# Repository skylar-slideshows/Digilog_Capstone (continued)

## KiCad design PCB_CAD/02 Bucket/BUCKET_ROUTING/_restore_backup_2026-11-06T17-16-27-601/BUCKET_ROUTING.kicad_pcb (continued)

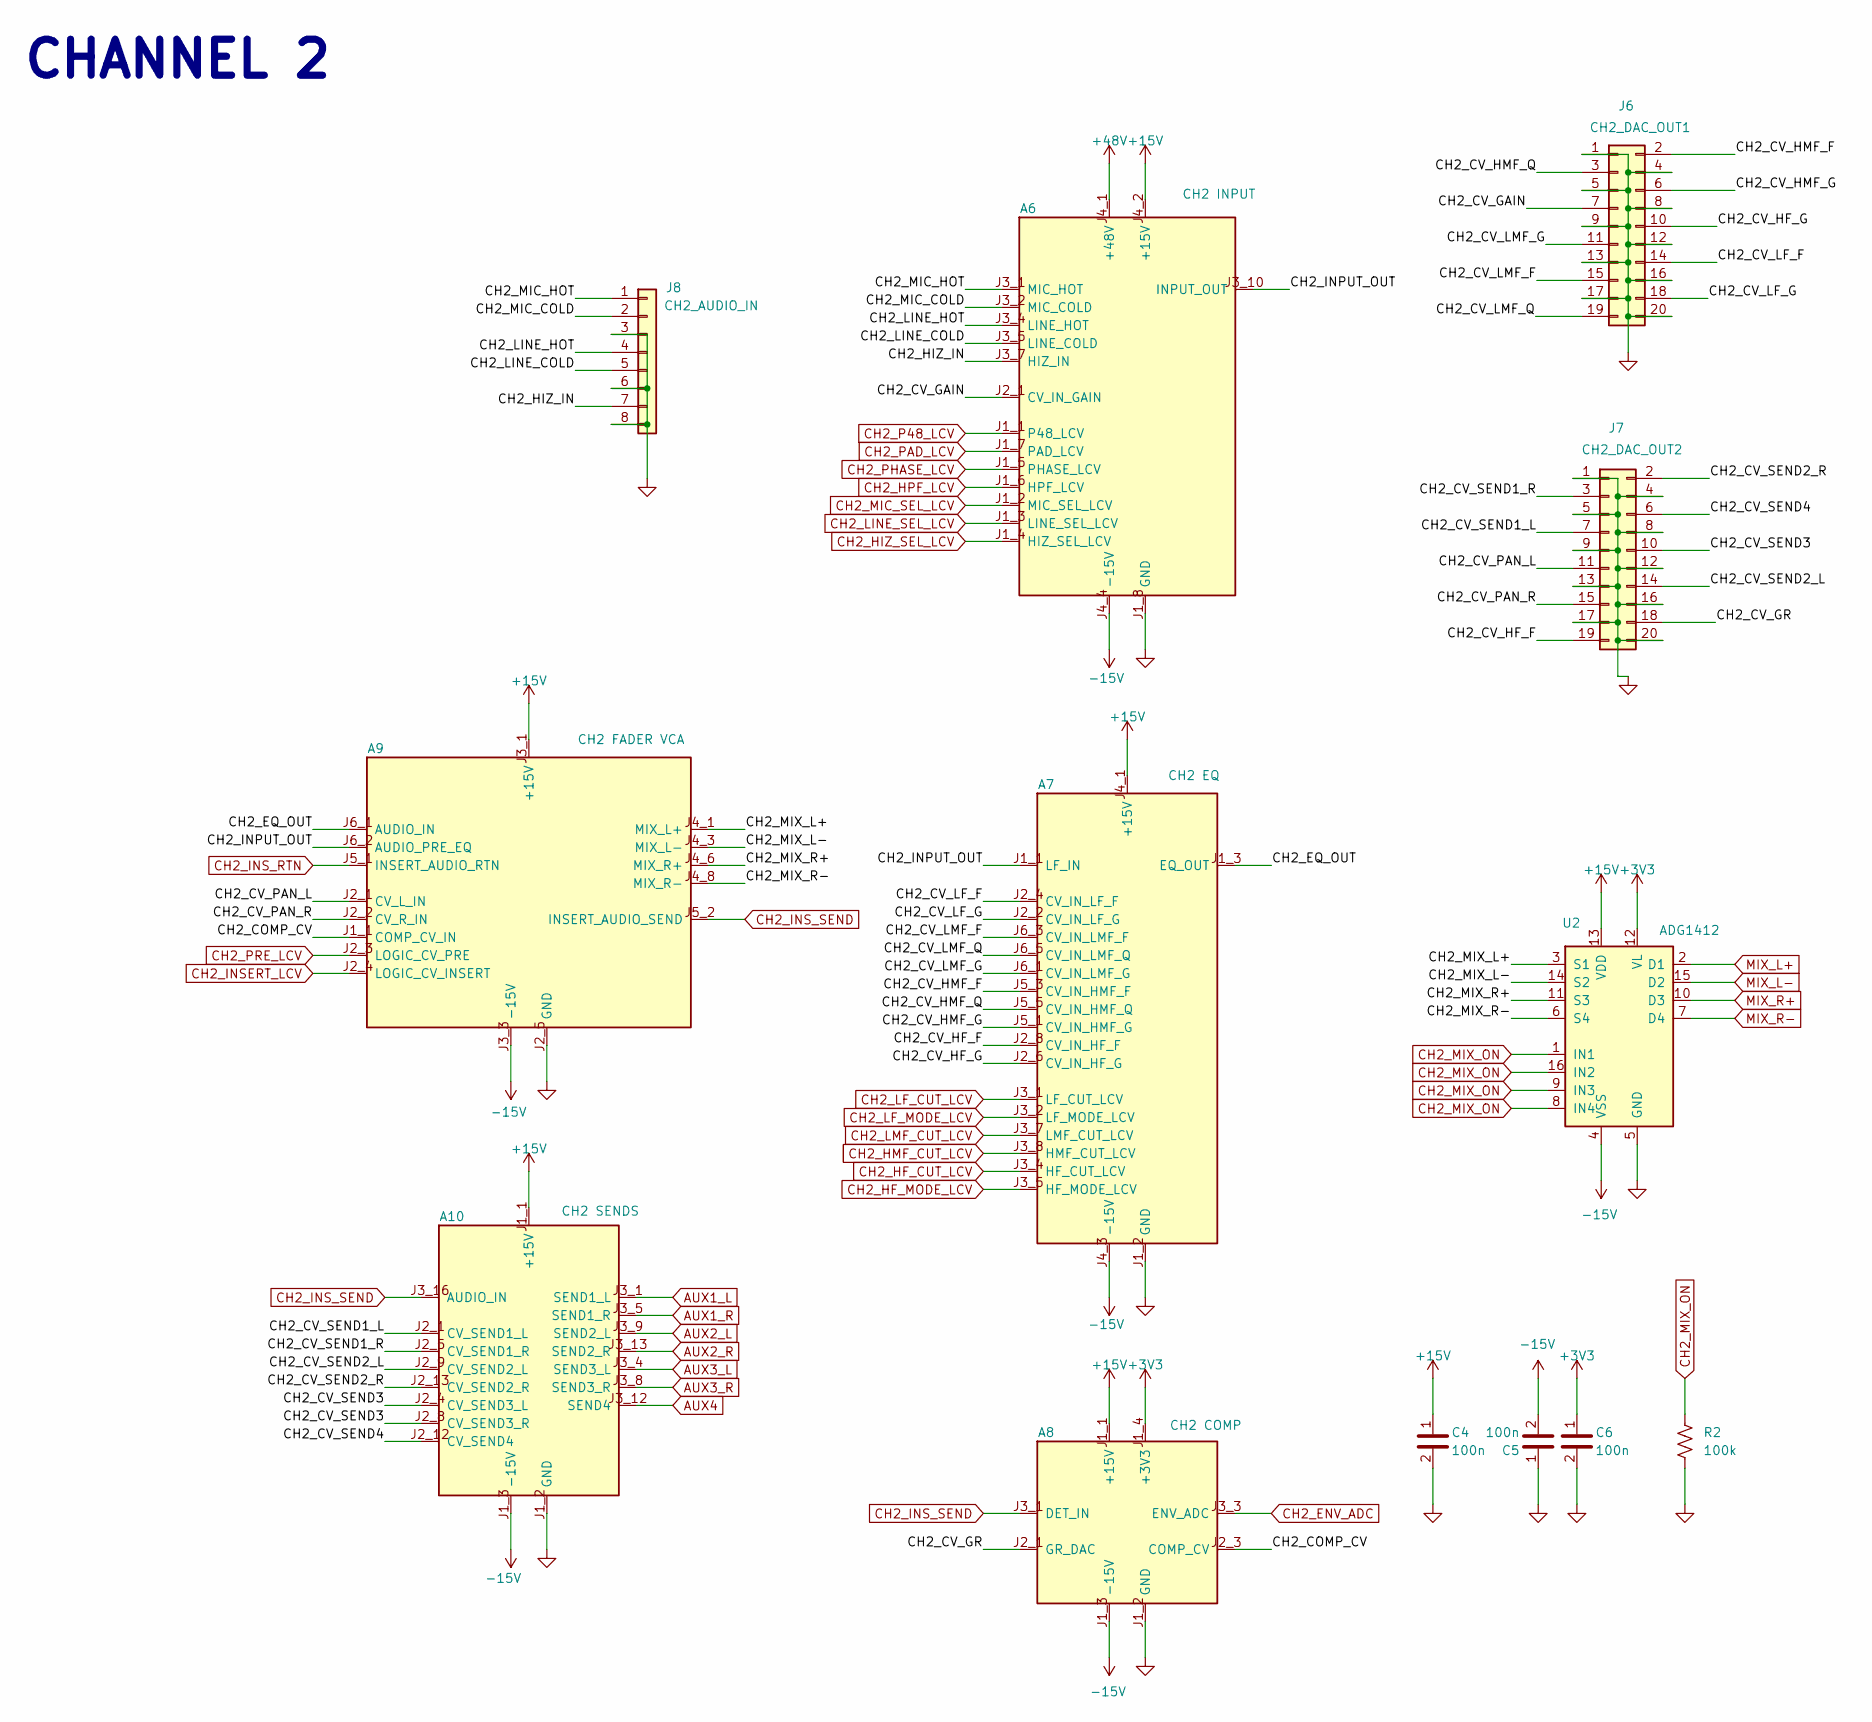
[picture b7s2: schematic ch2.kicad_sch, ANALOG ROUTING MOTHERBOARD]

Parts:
A6: CH2 INPUT; INPUT_CARD; LCSC dnp
A7: CH2 EQ; EQ_CARD; LCSC dnp
A8: CH2 COMP; COMP_CARD; LCSC dnp
A9: CH2 FADER VCA; FADER_VCA_CARD; LCSC dnp
A10: CH2 SENDS; SENDS_CARD; LCSC dnp
C4, C5, C6: 100n; C_0603_1608Metric; LCSC C1591
J6: CH2_DAC_OUT1; PinHeader_2x10_P1.27mm_Vertical; LCSC C42455943
J7: CH2_DAC_OUT2; PinHeader_2x10_P1.27mm_Vertical; LCSC C42455943
J8: CH2_AUDIO_IN; PinHeader_1x08_P2.54mm_Vertical; LCSC C54620384
R2: 100k; R_0603_1608Metric; LCSC C122538
U2: ADG1412; TSSOP-16_4.4x5mm_P0.65mm; LCSC C206604

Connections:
+3V3: A8.J1_4 (+3V3), C6.1, U2.12 (VL); also elsewhere on the board
+15V: A6.J4_2 (+15V), A7.J4_1 (+15V), A8.J1_1 (+15V), A9.J3_1 (+15V), A10.J1_1 (+15V), C4.1, U2.13 (VDD); also elsewhere on the board
+48V: A6.J4_1 (+48V); also elsewhere on the board
-15V: A6.J4_4 (-15V), A7.J4_3 (-15V), A8.J1_3 (-15V), A9.J3_3 (-15V), A10.J1_3 (-15V), C5.2, U2.4 (VSS); also elsewhere on the board
/CH2/CH2_COMP_CV: A8.J2_3 (COMP_CV), A9.J1_1 (COMP_CV_IN)
/CH2/CH2_CV_GAIN: A6.J2_1 (CV_IN_GAIN), J6.7
/CH2/CH2_CV_GR: A8.J2_1 (GR_DAC), J7.18
/CH2/CH2_CV_HF_F: A7.J2_8 (CV_IN_HF_F), J7.19
/CH2/CH2_CV_HF_G: A7.J2_6 (CV_IN_HF_G), J6.10
/CH2/CH2_CV_HMF_F: A7.J5_3 (CV_IN_HMF_F), J6.2
/CH2/CH2_CV_HMF_G: A7.J5_1 (CV_IN_HMF_G), J6.6
/CH2/CH2_CV_HMF_Q: A7.J5_5 (CV_IN_HMF_Q), J6.3
/CH2/CH2_CV_LF_F: A7.J2_4 (CV_IN_LF_F), J6.14
/CH2/CH2_CV_LF_G: A7.J2_2 (CV_IN_LF_G), J6.18
/CH2/CH2_CV_LMF_F: A7.J6_3 (CV_IN_LMF_F), J6.15
/CH2/CH2_CV_LMF_G: A7.J6_1 (CV_IN_LMF_G), J6.11
/CH2/CH2_CV_LMF_Q: A7.J6_5 (CV_IN_LMF_Q), J6.19
/CH2/CH2_CV_PAN_L: A9.J2_1 (CV_L_IN), J7.11
/CH2/CH2_CV_PAN_R: A9.J2_2 (CV_R_IN), J7.15
/CH2/CH2_CV_SEND1_L: A10.J2_1 (CV_SEND1_L), J7.7
/CH2/CH2_CV_SEND1_R: A10.J2_5 (CV_SEND1_R), J7.3
/CH2/CH2_CV_SEND2_L: A10.J2_9 (CV_SEND2_L), J7.14
/CH2/CH2_CV_SEND2_R: A10.J2_13 (CV_SEND2_R), J7.2
/CH2/CH2_CV_SEND3: A10.J2_4 (CV_SEND3_L), A10.J2_8 (CV_SEND3_R), J7.10
/CH2/CH2_CV_SEND4: A10.J2_12 (CV_SEND4), J7.6
/CH2/CH2_EQ_OUT: A7.J1_3 (EQ_OUT), A9.J6_1 (AUDIO_IN)
/CH2/CH2_HIZ_IN: A6.J3_7 (HIZ_IN), J8.7
/CH2/CH2_INPUT_OUT: A6.J3_10 (INPUT_OUT), A7.J1_1 (LF_IN), A9.J6_2 (AUDIO_PRE_EQ)
/CH2/CH2_LINE_COLD: A6.J3_5 (LINE_COLD), J8.5
/CH2/CH2_LINE_HOT: A6.J3_4 (LINE_HOT), J8.4
/CH2/CH2_MIC_COLD: A6.J3_2 (MIC_COLD), J8.2
/CH2/CH2_MIC_HOT: A6.J3_1 (MIC_HOT), J8.1
/CH2/CH2_MIX_L+: A9.J4_1 (MIX_L+), U2.3 (S1)
/CH2/CH2_MIX_L-: A9.J4_3 (MIX_L-), U2.14 (S2)
/CH2/CH2_MIX_R+: A9.J4_6 (MIX_R+), U2.11 (S3)
/CH2/CH2_MIX_R-: A9.J4_8 (MIX_R-), U2.6 (S4)
AUX1_L: A10.J3_1 (SEND1_L); also elsewhere on the board
AUX1_R: A10.J3_5 (SEND1_R); also elsewhere on the board
AUX2_L: A10.J3_9 (SEND2_L); also elsewhere on the board
AUX2_R: A10.J3_13 (SEND2_R); also elsewhere on the board
AUX3_L: A10.J3_4 (SEND3_L); also elsewhere on the board
AUX3_R: A10.J3_8 (SEND3_R); also elsewhere on the board
AUX4: A10.J3_12 (SEND4); also elsewhere on the board
CH2_ENV_ADC: A8.J3_3 (ENV_ADC); also elsewhere on the board
CH2_HF_CUT_LCV: A7.J3_4 (HF_CUT_LCV); also elsewhere on the board
CH2_HF_MODE_LCV: A7.J3_5 (HF_MODE_LCV); also elsewhere on the board
CH2_HIZ_SEL_LCV: A6.J1_4 (HIZ_SEL_LCV); also elsewhere on the board
CH2_HMF_CUT_LCV: A7.J3_8 (HMF_CUT_LCV); also elsewhere on the board
CH2_HPF_LCV: A6.J1_6 (HPF_LCV); also elsewhere on the board
CH2_INSERT_LCV: A9.J2_4 (LOGIC_CV_INSERT); also elsewhere on the board
CH2_INS_RTN: A9.J5_1 (INSERT_AUDIO_RTN); also elsewhere on the board
CH2_INS_SEND: A8.J3_1 (DET_IN), A9.J5_2 (INSERT_AUDIO_SEND), A10.J3_16 (AUDIO_IN); also elsewhere on the board
CH2_LF_CUT_LCV: A7.J3_1 (LF_CUT_LCV); also elsewhere on the board
CH2_LF_MODE_LCV: A7.J3_2 (LF_MODE_LCV); also elsewhere on the board
CH2_LINE_SEL_LCV: A6.J1_3 (LINE_SEL_LCV); also elsewhere on the board
CH2_LMF_CUT_LCV: A7.J3_7 (LMF_CUT_LCV); also elsewhere on the board
CH2_MIC_SEL_LCV: A6.J1_2 (MIC_SEL_LCV); also elsewhere on the board
CH2_MIX_ON: R2.1, U2.1 (IN1), U2.8 (IN4), U2.9 (IN3), U2.16 (IN2); also elsewhere on the board
CH2_P48_LCV: A6.J1_1 (P48_LCV); also elsewhere on the board
CH2_PAD_LCV: A6.J1_7 (PAD_LCV); also elsewhere on the board
CH2_PHASE_LCV: A6.J1_5 (PHASE_LCV); also elsewhere on the board
CH2_PRE_LCV: A9.J2_3 (LOGIC_CV_PRE); also elsewhere on the board
GND: A6.J1_8 (GND), A6.J2_2 (GND), A6.J3_3 (GND), A6.J3_6 (GND), A6.J3_8 (GND), A6.J3_9 (GND), A6.J4_3 (GND), A7.J1_2 (GND), A7.J1_4 (GND), A7.J2_1 (GND), A7.J2_3 (GND), A7.J2_5 (GND), A7.J2_7 (GND), A7.J3_3 (GND), A7.J3_6 (GND), A7.J4_2 (GND), A7.J5_2 (GND), A7.J5_4 (GND), A7.J5_6 (GND), A7.J6_2 (GND), A7.J6_4 (GND), A7.J6_6 (GND), A8.J1_2 (GND), A8.J2_2 (GND), A8.J2_4 (GND), A8.J3_2 (GND), A8.J3_4 (GND), A9.J1_2 (GND), A9.J2_5 (GND), A9.J3_2 (GND), A9.J4_2 (GND), A9.J4_4 (GND), A9.J4_5 (GND), A9.J4_7 (GND), A9.J5_3 (GND), A9.J6_3 (GND), A10.J1_2 (GND), A10.J2_2 (GND), A10.J2_3 (GND), A10.J2_6 (GND), A10.J2_7 (GND), A10.J2_10 (GND), A10.J2_11 (GND), A10.J2_14 (GND), A10.J3_2 (GND), A10.J3_3 (GND), A10.J3_6 (GND), A10.J3_7 (GND), A10.J3_10 (GND), A10.J3_11 (GND), A10.J3_14 (GND), A10.J3_15 (GND), C4.2, C5.1, C6.2, J6.1, J6.4, J6.5, J6.8, J6.9, J6.12, J6.13, J6.16, J6.17, J6.20, J7.1, J7.4, J7.5, J7.8, J7.9, J7.12, J7.13, J7.16, J7.17, J7.20, J8.3, J8.6, J8.8, R2.2, U2.5 (GND); also elsewhere on the board
MIX_L+: U2.2 (D1); also elsewhere on the board
MIX_L-: U2.15 (D2); also elsewhere on the board
MIX_R+: U2.10 (D3); also elsewhere on the board
MIX_R-: U2.7 (D4); also elsewhere on the board

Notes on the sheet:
CHANNEL 2

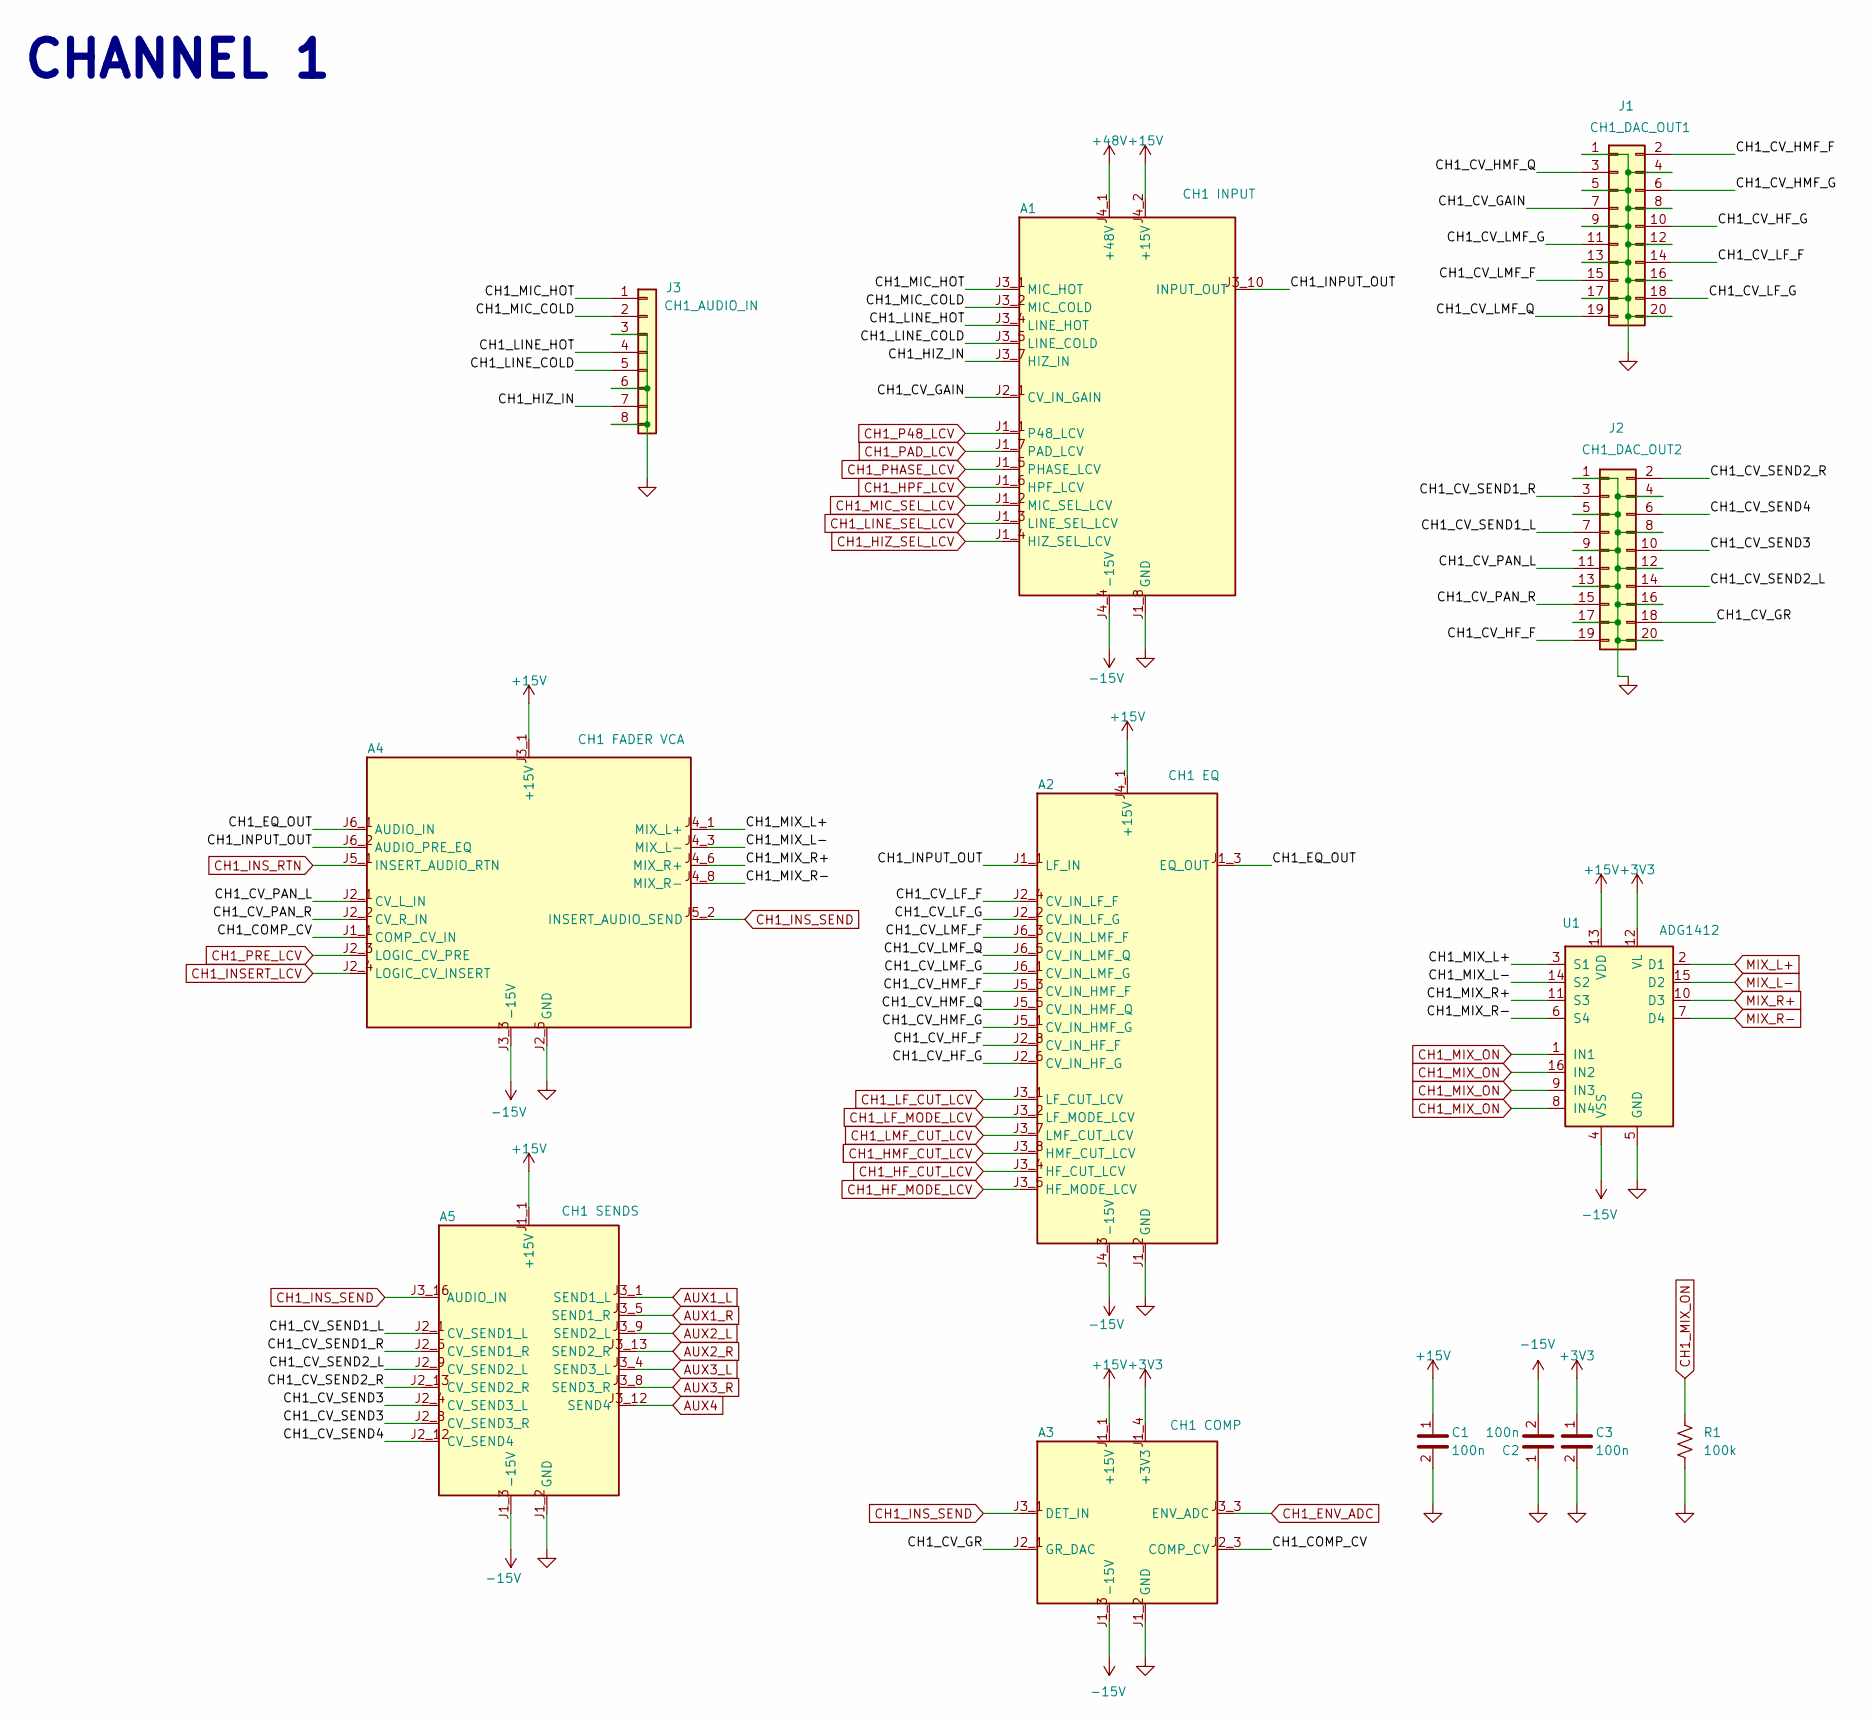
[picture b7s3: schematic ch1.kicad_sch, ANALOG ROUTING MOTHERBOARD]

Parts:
A1: CH1 INPUT; INPUT_CARD; LCSC dnp
A2: CH1 EQ; EQ_CARD; LCSC dnp
A3: CH1 COMP; COMP_CARD; LCSC dnp
A4: CH1 FADER VCA; FADER_VCA_CARD; LCSC dnp
A5: CH1 SENDS; SENDS_CARD; LCSC dnp
C1, C2, C3: 100n; C_0603_1608Metric
J1: CH1_DAC_OUT1; PinHeader_2x10_P1.27mm_Vertical
J2: CH1_DAC_OUT2; PinHeader_2x10_P1.27mm_Vertical
J3: CH1_AUDIO_IN; PinHeader_1x08_P2.54mm_Vertical
R1: 100k; R_0603_1608Metric
U1: ADG1412; TSSOP-16_4.4x5mm_P0.65mm

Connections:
+3V3: A3.J1_4 (+3V3), C3.1, U1.12 (VL); also elsewhere on the board
+15V: A1.J4_2 (+15V), A2.J4_1 (+15V), A3.J1_1 (+15V), A4.J3_1 (+15V), A5.J1_1 (+15V), C1.1, U1.13 (VDD); also elsewhere on the board
+48V: A1.J4_1 (+48V); also elsewhere on the board
-15V: A1.J4_4 (-15V), A2.J4_3 (-15V), A3.J1_3 (-15V), A4.J3_3 (-15V), A5.J1_3 (-15V), C2.2, U1.4 (VSS); also elsewhere on the board
/CH1/CH1_COMP_CV: A3.J2_3 (COMP_CV), A4.J1_1 (COMP_CV_IN)
/CH1/CH1_CV_GAIN: A1.J2_1 (CV_IN_GAIN), J1.7
/CH1/CH1_CV_GR: A3.J2_1 (GR_DAC), J2.18
/CH1/CH1_CV_HF_F: A2.J2_8 (CV_IN_HF_F), J2.19
/CH1/CH1_CV_HF_G: A2.J2_6 (CV_IN_HF_G), J1.10
/CH1/CH1_CV_HMF_F: A2.J5_3 (CV_IN_HMF_F), J1.2
/CH1/CH1_CV_HMF_G: A2.J5_1 (CV_IN_HMF_G), J1.6
/CH1/CH1_CV_HMF_Q: A2.J5_5 (CV_IN_HMF_Q), J1.3
/CH1/CH1_CV_LF_F: A2.J2_4 (CV_IN_LF_F), J1.14
/CH1/CH1_CV_LF_G: A2.J2_2 (CV_IN_LF_G), J1.18
/CH1/CH1_CV_LMF_F: A2.J6_3 (CV_IN_LMF_F), J1.15
/CH1/CH1_CV_LMF_G: A2.J6_1 (CV_IN_LMF_G), J1.11
/CH1/CH1_CV_LMF_Q: A2.J6_5 (CV_IN_LMF_Q), J1.19
/CH1/CH1_CV_PAN_L: A4.J2_1 (CV_L_IN), J2.11
/CH1/CH1_CV_PAN_R: A4.J2_2 (CV_R_IN), J2.15
/CH1/CH1_CV_SEND1_L: A5.J2_1 (CV_SEND1_L), J2.7
/CH1/CH1_CV_SEND1_R: A5.J2_5 (CV_SEND1_R), J2.3
/CH1/CH1_CV_SEND2_L: A5.J2_9 (CV_SEND2_L), J2.14
/CH1/CH1_CV_SEND2_R: A5.J2_13 (CV_SEND2_R), J2.2
/CH1/CH1_CV_SEND3: A5.J2_4 (CV_SEND3_L), A5.J2_8 (CV_SEND3_R), J2.10
/CH1/CH1_CV_SEND4: A5.J2_12 (CV_SEND4), J2.6
/CH1/CH1_EQ_OUT: A2.J1_3 (EQ_OUT), A4.J6_1 (AUDIO_IN)
/CH1/CH1_HIZ_IN: A1.J3_7 (HIZ_IN), J3.7
/CH1/CH1_INPUT_OUT: A1.J3_10 (INPUT_OUT), A2.J1_1 (LF_IN), A4.J6_2 (AUDIO_PRE_EQ)
/CH1/CH1_LINE_COLD: A1.J3_5 (LINE_COLD), J3.5
/CH1/CH1_LINE_HOT: A1.J3_4 (LINE_HOT), J3.4
/CH1/CH1_MIC_COLD: A1.J3_2 (MIC_COLD), J3.2
/CH1/CH1_MIC_HOT: A1.J3_1 (MIC_HOT), J3.1
/CH1/CH1_MIX_L+: A4.J4_1 (MIX_L+), U1.3 (S1)
/CH1/CH1_MIX_L-: A4.J4_3 (MIX_L-), U1.14 (S2)
/CH1/CH1_MIX_R+: A4.J4_6 (MIX_R+), U1.11 (S3)
/CH1/CH1_MIX_R-: A4.J4_8 (MIX_R-), U1.6 (S4)
AUX1_L: A5.J3_1 (SEND1_L); also elsewhere on the board
AUX1_R: A5.J3_5 (SEND1_R); also elsewhere on the board
AUX2_L: A5.J3_9 (SEND2_L); also elsewhere on the board
AUX2_R: A5.J3_13 (SEND2_R); also elsewhere on the board
AUX3_L: A5.J3_4 (SEND3_L); also elsewhere on the board
AUX3_R: A5.J3_8 (SEND3_R); also elsewhere on the board
AUX4: A5.J3_12 (SEND4); also elsewhere on the board
CH1_ENV_ADC: A3.J3_3 (ENV_ADC); also elsewhere on the board
CH1_HF_CUT_LCV: A2.J3_4 (HF_CUT_LCV); also elsewhere on the board
CH1_HF_MODE_LCV: A2.J3_5 (HF_MODE_LCV); also elsewhere on the board
CH1_HIZ_SEL_LCV: A1.J1_4 (HIZ_SEL_LCV); also elsewhere on the board
CH1_HMF_CUT_LCV: A2.J3_8 (HMF_CUT_LCV); also elsewhere on the board
CH1_HPF_LCV: A1.J1_6 (HPF_LCV); also elsewhere on the board
CH1_INSERT_LCV: A4.J2_4 (LOGIC_CV_INSERT); also elsewhere on the board
CH1_INS_RTN: A4.J5_1 (INSERT_AUDIO_RTN); also elsewhere on the board
CH1_INS_SEND: A3.J3_1 (DET_IN), A4.J5_2 (INSERT_AUDIO_SEND), A5.J3_16 (AUDIO_IN); also elsewhere on the board
CH1_LF_CUT_LCV: A2.J3_1 (LF_CUT_LCV); also elsewhere on the board
CH1_LF_MODE_LCV: A2.J3_2 (LF_MODE_LCV); also elsewhere on the board
CH1_LINE_SEL_LCV: A1.J1_3 (LINE_SEL_LCV); also elsewhere on the board
CH1_LMF_CUT_LCV: A2.J3_7 (LMF_CUT_LCV); also elsewhere on the board
CH1_MIC_SEL_LCV: A1.J1_2 (MIC_SEL_LCV); also elsewhere on the board
CH1_MIX_ON: R1.1, U1.1 (IN1), U1.8 (IN4), U1.9 (IN3), U1.16 (IN2); also elsewhere on the board
CH1_P48_LCV: A1.J1_1 (P48_LCV); also elsewhere on the board
CH1_PAD_LCV: A1.J1_7 (PAD_LCV); also elsewhere on the board
CH1_PHASE_LCV: A1.J1_5 (PHASE_LCV); also elsewhere on the board
CH1_PRE_LCV: A4.J2_3 (LOGIC_CV_PRE); also elsewhere on the board
GND: A1.J1_8 (GND), A1.J2_2 (GND), A1.J3_3 (GND), A1.J3_6 (GND), A1.J3_8 (GND), A1.J3_9 (GND), A1.J4_3 (GND), A2.J1_2 (GND), A2.J1_4 (GND), A2.J2_1 (GND), A2.J2_3 (GND), A2.J2_5 (GND), A2.J2_7 (GND), A2.J3_3 (GND), A2.J3_6 (GND), A2.J4_2 (GND), A2.J5_2 (GND), A2.J5_4 (GND), A2.J5_6 (GND), A2.J6_2 (GND), A2.J6_4 (GND), A2.J6_6 (GND), A3.J1_2 (GND), A3.J2_2 (GND), A3.J2_4 (GND), A3.J3_2 (GND), A3.J3_4 (GND), A4.J1_2 (GND), A4.J2_5 (GND), A4.J3_2 (GND), A4.J4_2 (GND), A4.J4_4 (GND), A4.J4_5 (GND), A4.J4_7 (GND), A4.J5_3 (GND), A4.J6_3 (GND), A5.J1_2 (GND), A5.J2_2 (GND), A5.J2_3 (GND), A5.J2_6 (GND), A5.J2_7 (GND), A5.J2_10 (GND), A5.J2_11 (GND), A5.J2_14 (GND), A5.J3_2 (GND), A5.J3_3 (GND), A5.J3_6 (GND), A5.J3_7 (GND), A5.J3_10 (GND), A5.J3_11 (GND), A5.J3_14 (GND), A5.J3_15 (GND), C1.2, C2.1, C3.2, J1.1, J1.4, J1.5, J1.8, J1.9, J1.12, J1.13, J1.16, J1.17, J1.20, J2.1, J2.4, J2.5, J2.8, J2.9, J2.12, J2.13, J2.16, J2.17, J2.20, J3.3, J3.6, J3.8, R1.2, U1.5 (GND); also elsewhere on the board
MIX_L+: U1.2 (D1); also elsewhere on the board
MIX_L-: U1.15 (D2); also elsewhere on the board
MIX_R+: U1.10 (D3); also elsewhere on the board
MIX_R-: U1.7 (D4); also elsewhere on the board

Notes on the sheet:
CHANNEL 1

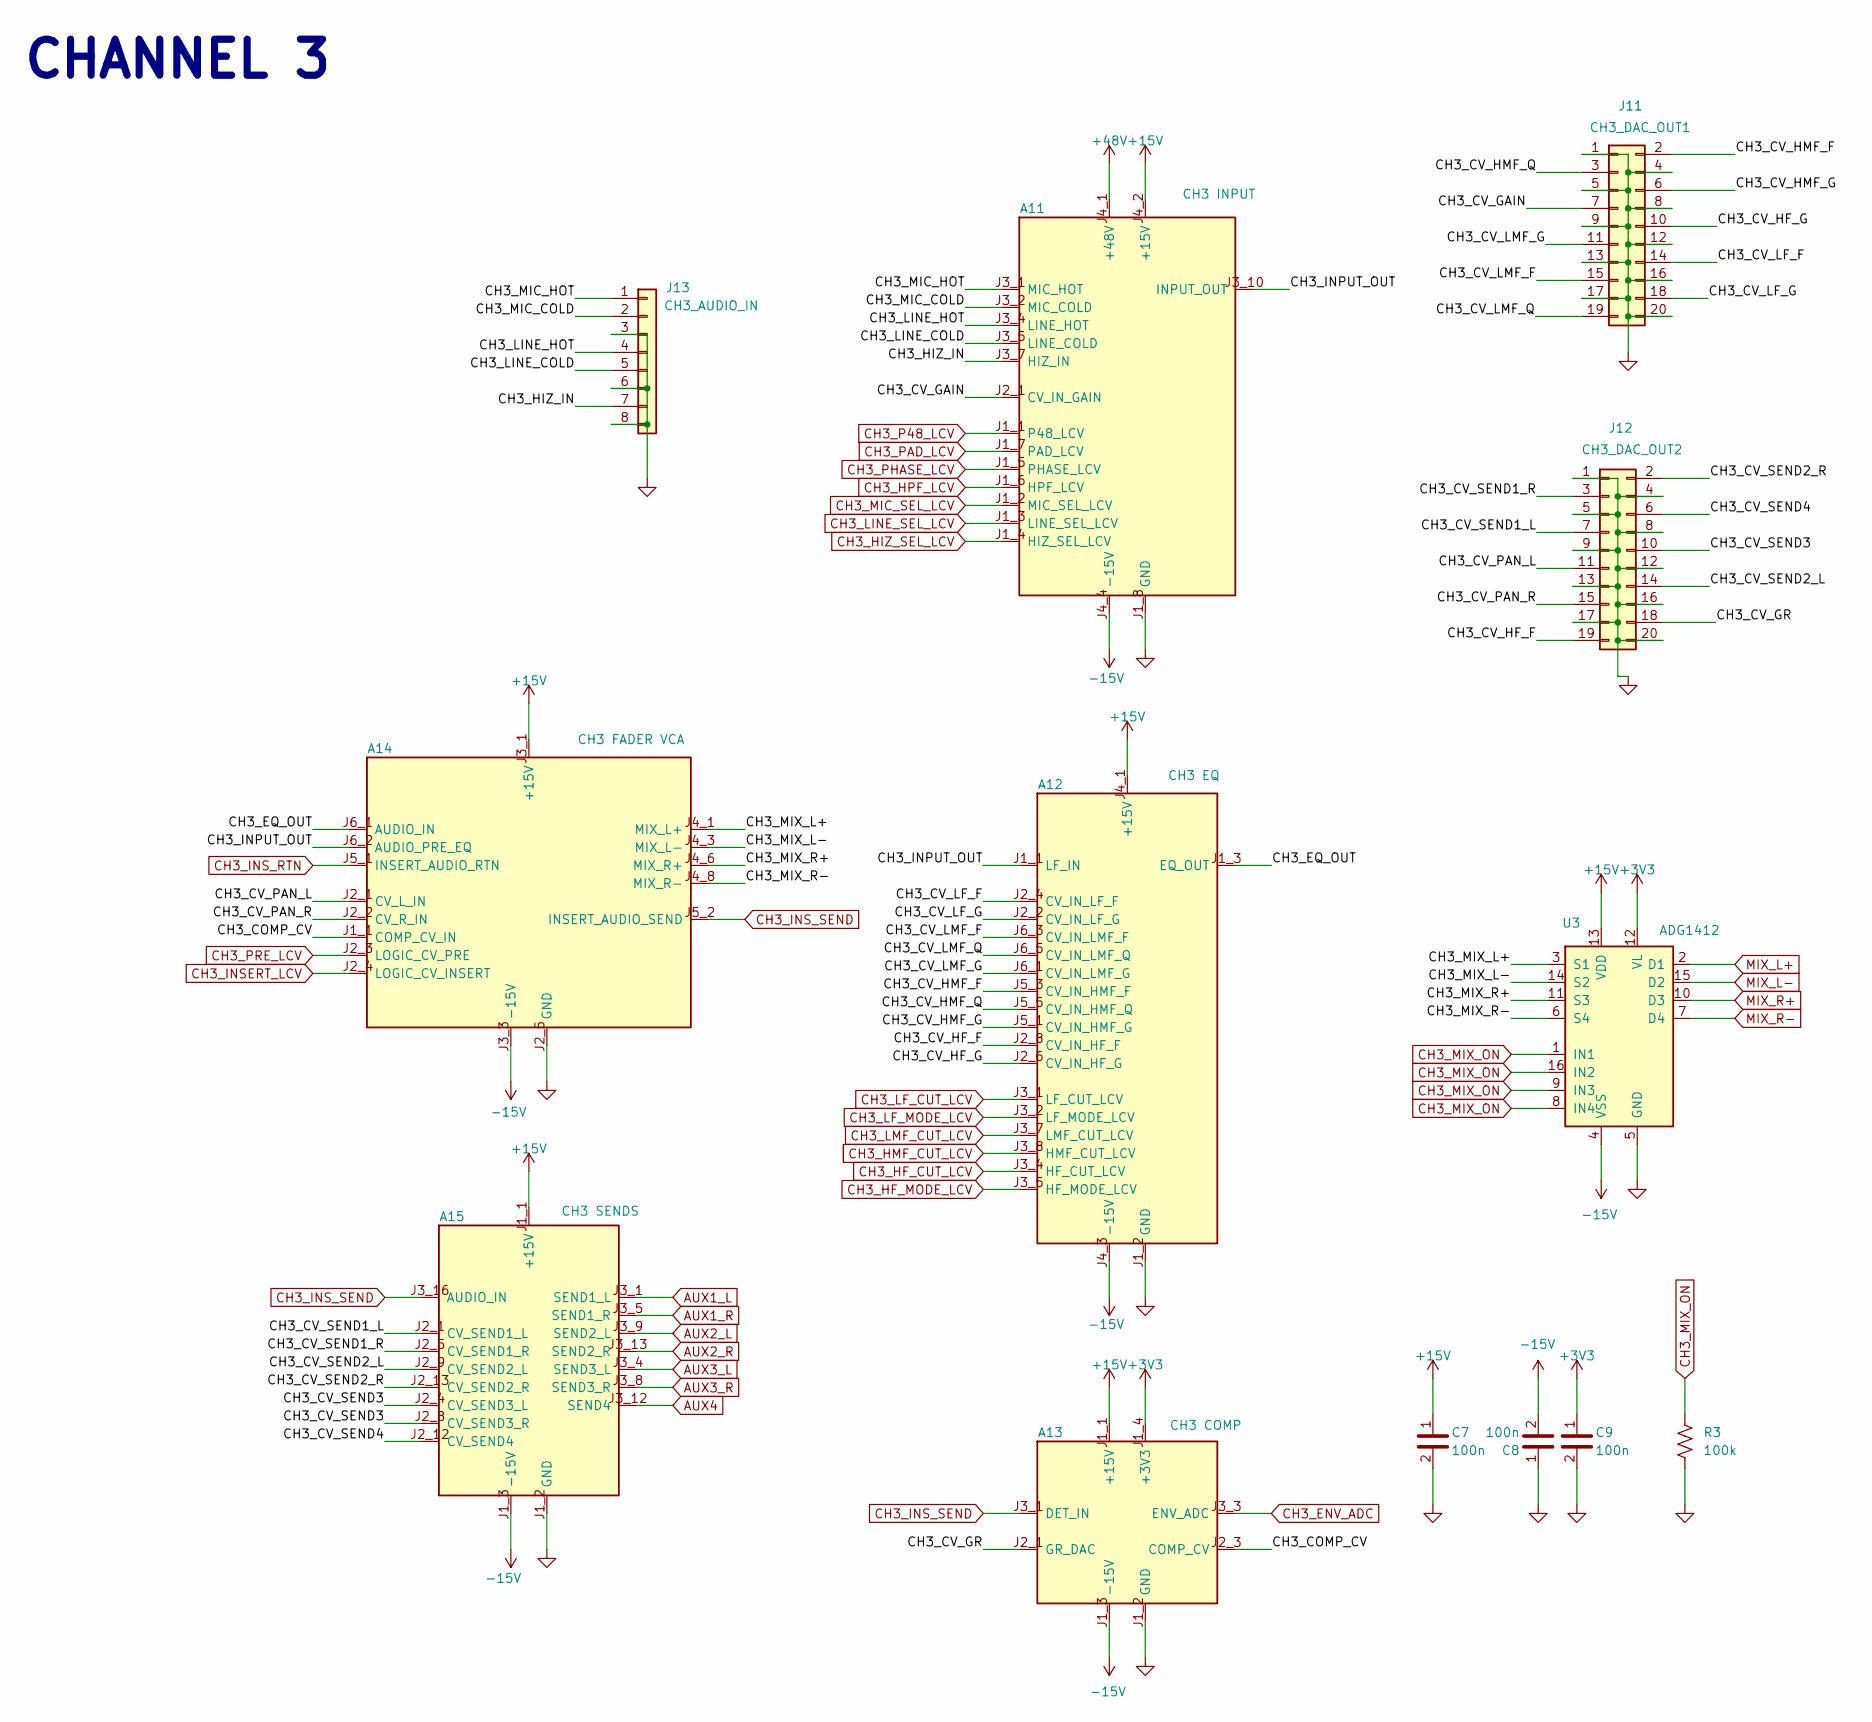
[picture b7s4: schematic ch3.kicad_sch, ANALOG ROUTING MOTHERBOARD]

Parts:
A11: CH3 INPUT; INPUT_CARD; LCSC dnp
A12: CH3 EQ; EQ_CARD; LCSC dnp
A13: CH3 COMP; COMP_CARD; LCSC dnp
A14: CH3 FADER VCA; FADER_VCA_CARD; LCSC dnp
A15: CH3 SENDS; SENDS_CARD; LCSC dnp
C7, C8, C9: 100n; C_0603_1608Metric
J11: CH3_DAC_OUT1; PinHeader_2x10_P1.27mm_Vertical
J12: CH3_DAC_OUT2; PinHeader_2x10_P1.27mm_Vertical
J13: CH3_AUDIO_IN; PinHeader_1x08_P2.54mm_Vertical
R3: 100k; R_0603_1608Metric
U3: ADG1412; TSSOP-16_4.4x5mm_P0.65mm

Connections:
+3V3: A13.J1_4 (+3V3), C9.1, U3.12 (VL); also elsewhere on the board
+15V: A11.J4_2 (+15V), A12.J4_1 (+15V), A13.J1_1 (+15V), A14.J3_1 (+15V), A15.J1_1 (+15V), C7.1, U3.13 (VDD); also elsewhere on the board
+48V: A11.J4_1 (+48V); also elsewhere on the board
-15V: A11.J4_4 (-15V), A12.J4_3 (-15V), A13.J1_3 (-15V), A14.J3_3 (-15V), A15.J1_3 (-15V), C8.2, U3.4 (VSS); also elsewhere on the board
/CH3/CH3_COMP_CV: A13.J2_3 (COMP_CV), A14.J1_1 (COMP_CV_IN)
/CH3/CH3_CV_GAIN: A11.J2_1 (CV_IN_GAIN), J11.7
/CH3/CH3_CV_GR: A13.J2_1 (GR_DAC), J12.18
/CH3/CH3_CV_HF_F: A12.J2_8 (CV_IN_HF_F), J12.19
/CH3/CH3_CV_HF_G: A12.J2_6 (CV_IN_HF_G), J11.10
/CH3/CH3_CV_HMF_F: A12.J5_3 (CV_IN_HMF_F), J11.2
/CH3/CH3_CV_HMF_G: A12.J5_1 (CV_IN_HMF_G), J11.6
/CH3/CH3_CV_HMF_Q: A12.J5_5 (CV_IN_HMF_Q), J11.3
/CH3/CH3_CV_LF_F: A12.J2_4 (CV_IN_LF_F), J11.14
/CH3/CH3_CV_LF_G: A12.J2_2 (CV_IN_LF_G), J11.18
/CH3/CH3_CV_LMF_F: A12.J6_3 (CV_IN_LMF_F), J11.15
/CH3/CH3_CV_LMF_G: A12.J6_1 (CV_IN_LMF_G), J11.11
/CH3/CH3_CV_LMF_Q: A12.J6_5 (CV_IN_LMF_Q), J11.19
/CH3/CH3_CV_PAN_L: A14.J2_1 (CV_L_IN), J12.11
/CH3/CH3_CV_PAN_R: A14.J2_2 (CV_R_IN), J12.15
/CH3/CH3_CV_SEND1_L: A15.J2_1 (CV_SEND1_L), J12.7
/CH3/CH3_CV_SEND1_R: A15.J2_5 (CV_SEND1_R), J12.3
/CH3/CH3_CV_SEND2_L: A15.J2_9 (CV_SEND2_L), J12.14
/CH3/CH3_CV_SEND2_R: A15.J2_13 (CV_SEND2_R), J12.2
/CH3/CH3_CV_SEND3: A15.J2_4 (CV_SEND3_L), A15.J2_8 (CV_SEND3_R), J12.10
/CH3/CH3_CV_SEND4: A15.J2_12 (CV_SEND4), J12.6
/CH3/CH3_EQ_OUT: A12.J1_3 (EQ_OUT), A14.J6_1 (AUDIO_IN)
/CH3/CH3_HIZ_IN: A11.J3_7 (HIZ_IN), J13.7
/CH3/CH3_INPUT_OUT: A11.J3_10 (INPUT_OUT), A12.J1_1 (LF_IN), A14.J6_2 (AUDIO_PRE_EQ)
/CH3/CH3_LINE_COLD: A11.J3_5 (LINE_COLD), J13.5
/CH3/CH3_LINE_HOT: A11.J3_4 (LINE_HOT), J13.4
/CH3/CH3_MIC_COLD: A11.J3_2 (MIC_COLD), J13.2
/CH3/CH3_MIC_HOT: A11.J3_1 (MIC_HOT), J13.1
/CH3/CH3_MIX_L+: A14.J4_1 (MIX_L+), U3.3 (S1)
/CH3/CH3_MIX_L-: A14.J4_3 (MIX_L-), U3.14 (S2)
/CH3/CH3_MIX_R+: A14.J4_6 (MIX_R+), U3.11 (S3)
/CH3/CH3_MIX_R-: A14.J4_8 (MIX_R-), U3.6 (S4)
AUX1_L: A15.J3_1 (SEND1_L); also elsewhere on the board
AUX1_R: A15.J3_5 (SEND1_R); also elsewhere on the board
AUX2_L: A15.J3_9 (SEND2_L); also elsewhere on the board
AUX2_R: A15.J3_13 (SEND2_R); also elsewhere on the board
AUX3_L: A15.J3_4 (SEND3_L); also elsewhere on the board
AUX3_R: A15.J3_8 (SEND3_R); also elsewhere on the board
AUX4: A15.J3_12 (SEND4); also elsewhere on the board
CH3_ENV_ADC: A13.J3_3 (ENV_ADC); also elsewhere on the board
CH3_HF_CUT_LCV: A12.J3_4 (HF_CUT_LCV); also elsewhere on the board
CH3_HF_MODE_LCV: A12.J3_5 (HF_MODE_LCV); also elsewhere on the board
CH3_HIZ_SEL_LCV: A11.J1_4 (HIZ_SEL_LCV); also elsewhere on the board
CH3_HMF_CUT_LCV: A12.J3_8 (HMF_CUT_LCV); also elsewhere on the board
CH3_HPF_LCV: A11.J1_6 (HPF_LCV); also elsewhere on the board
CH3_INSERT_LCV: A14.J2_4 (LOGIC_CV_INSERT); also elsewhere on the board
CH3_INS_RTN: A14.J5_1 (INSERT_AUDIO_RTN); also elsewhere on the board
CH3_INS_SEND: A13.J3_1 (DET_IN), A14.J5_2 (INSERT_AUDIO_SEND), A15.J3_16 (AUDIO_IN); also elsewhere on the board
CH3_LF_CUT_LCV: A12.J3_1 (LF_CUT_LCV); also elsewhere on the board
CH3_LF_MODE_LCV: A12.J3_2 (LF_MODE_LCV); also elsewhere on the board
CH3_LINE_SEL_LCV: A11.J1_3 (LINE_SEL_LCV); also elsewhere on the board
CH3_LMF_CUT_LCV: A12.J3_7 (LMF_CUT_LCV); also elsewhere on the board
CH3_MIC_SEL_LCV: A11.J1_2 (MIC_SEL_LCV); also elsewhere on the board
CH3_MIX_ON: R3.1, U3.1 (IN1), U3.8 (IN4), U3.9 (IN3), U3.16 (IN2); also elsewhere on the board
CH3_P48_LCV: A11.J1_1 (P48_LCV); also elsewhere on the board
CH3_PAD_LCV: A11.J1_7 (PAD_LCV); also elsewhere on the board
CH3_PHASE_LCV: A11.J1_5 (PHASE_LCV); also elsewhere on the board
CH3_PRE_LCV: A14.J2_3 (LOGIC_CV_PRE); also elsewhere on the board
GND: A11.J1_8 (GND), A11.J2_2 (GND), A11.J3_3 (GND), A11.J3_6 (GND), A11.J3_8 (GND), A11.J3_9 (GND), A11.J4_3 (GND), A12.J1_2 (GND), A12.J1_4 (GND), A12.J2_1 (GND), A12.J2_3 (GND), A12.J2_5 (GND), A12.J2_7 (GND), A12.J3_3 (GND), A12.J3_6 (GND), A12.J4_2 (GND), A12.J5_2 (GND), A12.J5_4 (GND), A12.J5_6 (GND), A12.J6_2 (GND), A12.J6_4 (GND), A12.J6_6 (GND), A13.J1_2 (GND), A13.J2_2 (GND), A13.J2_4 (GND), A13.J3_2 (GND), A13.J3_4 (GND), A14.J1_2 (GND), A14.J2_5 (GND), A14.J3_2 (GND), A14.J4_2 (GND), A14.J4_4 (GND), A14.J4_5 (GND), A14.J4_7 (GND), A14.J5_3 (GND), A14.J6_3 (GND), A15.J1_2 (GND), A15.J2_2 (GND), A15.J2_3 (GND), A15.J2_6 (GND), A15.J2_7 (GND), A15.J2_10 (GND), A15.J2_11 (GND), A15.J2_14 (GND), A15.J3_2 (GND), A15.J3_3 (GND), A15.J3_6 (GND), A15.J3_7 (GND), A15.J3_10 (GND), A15.J3_11 (GND), A15.J3_14 (GND), A15.J3_15 (GND), C7.2, C8.1, C9.2, J11.1, J11.4, J11.5, J11.8, J11.9, J11.12, J11.13, J11.16, J11.17, J11.20, J12.1, J12.4, J12.5, J12.8, J12.9, J12.12, J12.13, J12.16, J12.17, J12.20, J13.3, J13.6, J13.8, R3.2, U3.5 (GND); also elsewhere on the board
MIX_L+: U3.2 (D1); also elsewhere on the board
MIX_L-: U3.15 (D2); also elsewhere on the board
MIX_R+: U3.10 (D3); also elsewhere on the board
MIX_R-: U3.7 (D4); also elsewhere on the board

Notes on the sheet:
CHANNEL 3

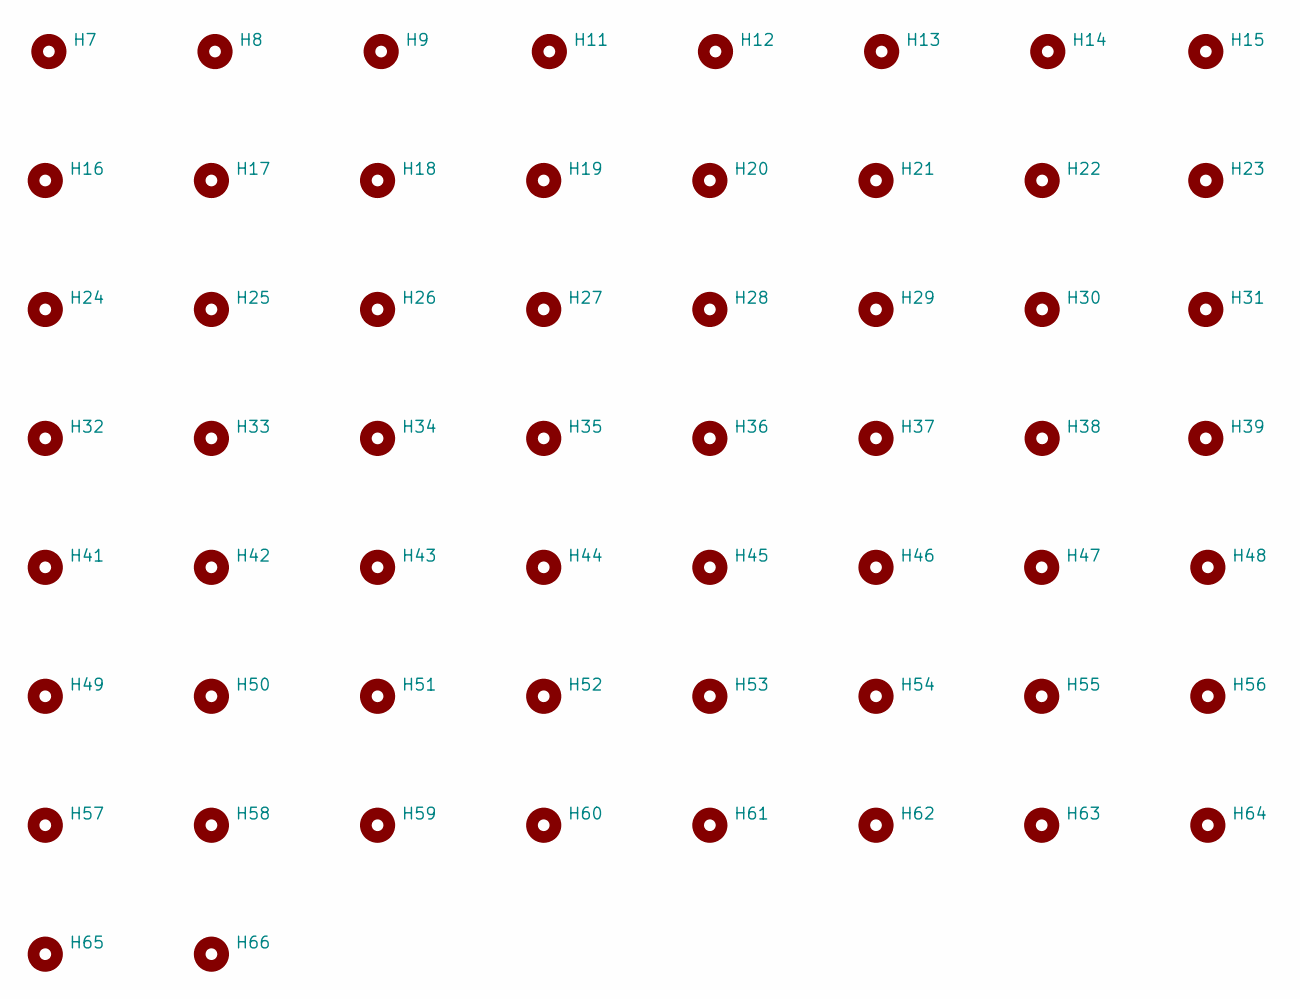
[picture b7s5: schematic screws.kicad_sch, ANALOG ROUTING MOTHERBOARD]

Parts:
H7, H8, H9, H11, H12, H13, H14, H15, H16, H17, H18, H19, H20, H21, H22, H23, H24, H25, H26, H27, H28, H29, H30, H31, H32, H33, H34, H35, H36, H37, H38, H39, H41, H42, H43, H44, H45, H46, H47, H48, H49, H50, H51, H52, H53, H54, H55, H56, H57, H58, H59, H60, H61, H62, H63, H64, H65, H66: MountingHole; MountingHole_2.2mm_M2; LCSC dnp
